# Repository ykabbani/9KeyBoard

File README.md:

# 9-KeyBoard - Custom Mechanical Keyboard

## Project Description

This project was my first attempt at designing and creating a fully functional PCB. The goal of this project was to create a prototype board - hence the 9 keys only, for what will be a full sized keyboard at some point in the future. Once the functionality is verified, the focus will divert to the 60% version of the keyboard (60% refers to 60% of a full sized keyboard, aka keyboard without the numpad or the function key row).

## Schematic

The schematic of the 9-KeyBoard is split into 4 different sections: uC, USB Interface, LED controller, and finally the keyboard's physical keys. Once the functionality of the 9-KeyBoard is verified, the only thing that will need to be changed is the key matrix. The schematic can be seen below: 

## PCB Layout

The component placement on the PCB is necessary after finishing the schematic. The components need to be placed in an optimal manner and the traces need to be routed to connect all the components together. This results in the following PCB and PCB render:

PCB Layout                 |  Top View of Render       |   Bottom View of Render
:-------------------------:|:-------------------------:|:-------------------------:
 |   | 

(Note that the missing components in the renders are due to the use of component libraries that do not contain models to be used in the renders) 

## Fabricated PCB

The final iteration of the prototype 9-KeyBoard was sent out to a fab house and once it arrived all traces were tested for continuity. Then, all components were installed and soldered with a hot air station. This was my first attempt at soldering with a hot air station, so it was not the cleanest job ever.

Bare PCB                   | Assembled & Soldered PCB             
:-------------------------:|:-------------------------:
 | 

## 9-KeyBoard RGB Demo

After verifying that everything was soldered properly, the 9-KeyBoard was plugged into the computer and the OS was flashed using a hex flasher. The ATMEGA32U4 uC comes from the factory with DFU (default bootloader), so flashing it was straight forward. Below is an RGB demo of it.

The 8 key was programmed to function as an RGB cycle button, while the 9 key was programmed to toggle RGB on/off.

RGB Demo                   |
:-------------------------:|
<video src="https://user-images.githubusercontent.com/26261828/186813127-bb65a537-f33c-4e9b-bb25-f617e034cc23.mp4" width="250" /> |

Notice that PCB had to be flipped 180 degrees so that the light can shine through the legends on the keycaps. This is due to a design flaw, as the RGB LEDs need to be placed directly above the switches rather than below them (since the legends are usually located on the upper-most edge of the keycap).

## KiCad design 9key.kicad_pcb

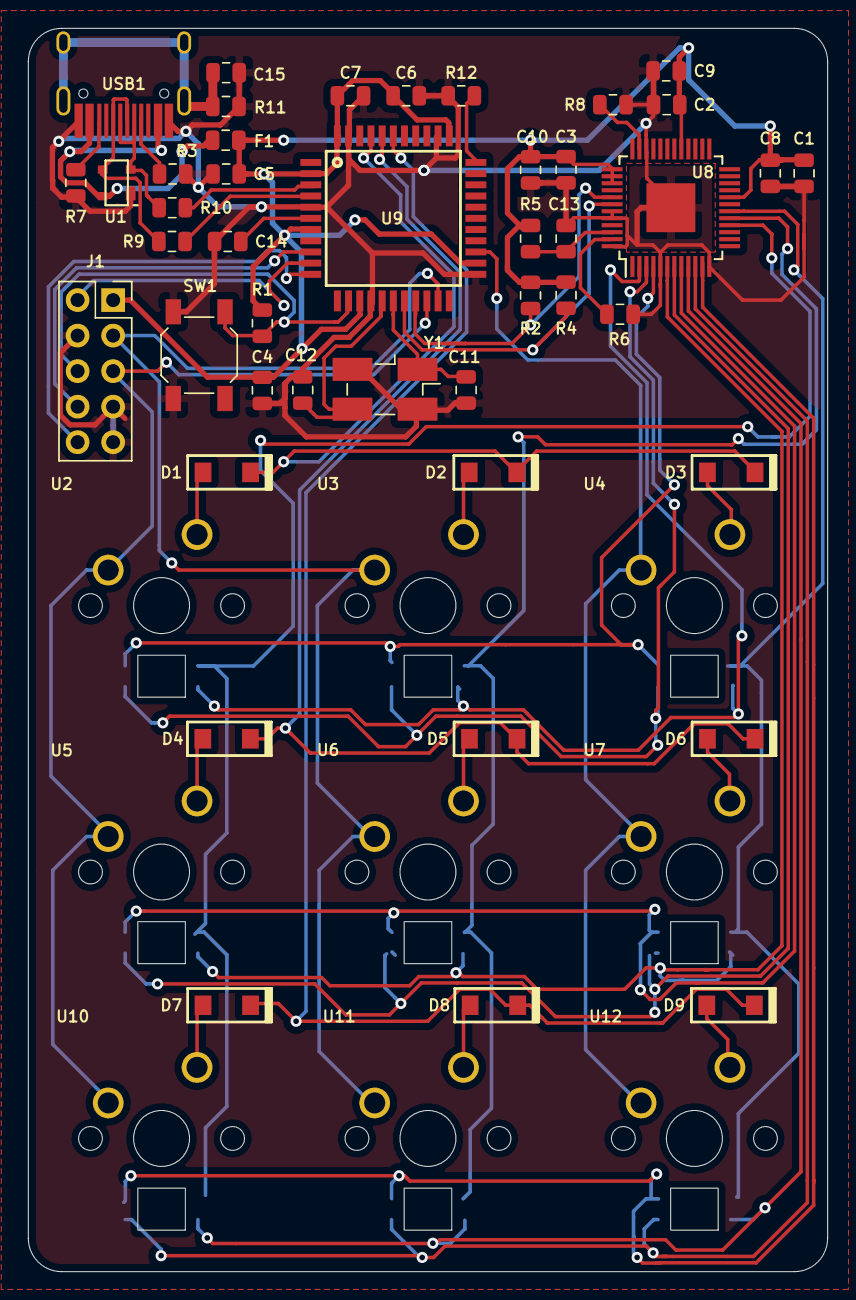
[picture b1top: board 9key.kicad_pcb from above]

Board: 2 copper layers, 57.2 x 88.9 mm, 53 parts (0 on the bottom side), 50 nets.

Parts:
C1, C2, C3: 0.47uF; C_0805_2012Metric
C4, C5, C6, C8, C9, C10: 0.1uF; C_0805_2012Metric
C7: 10uF; C_0805_2012Metric
C11, C12: 22pF; C_0805_2012Metric
C13, C14: 1uF; C_0805_2012Metric
C15: 4.7nF; C_0805_2012Metric
D1, D2, D3, D4, D5, D6, D7, D8, D9: D_Small; D_SOD123
F1: Polyfuse_Small; Fuse_0805_2012Metric
J1: Conn_02x05_Odd_Even; PinSocket_2x05_P2.54mm_Vertical
R1, R5, R12: 10k; R_0805_2012Metric
R2: 1k; R_0805_2012Metric
R3, R7: 5.1k; R_0805_2012Metric
R4: 1K; R_0805_2012Metric
R6: 100k; R_0805_2012Metric
R8: 20k; R_0805_2012Metric
R9, R10: 22; R_0805_2012Metric
R11: 1M; R_0805_2012Metric
SW1: SW_Push; SW_SPST_SKQG_WithStem
U1: PRTR5V0U2X; SOT-143B
U2, U3, U4, U5, U6, U7, U10, U11, U12: Cherry_MX_RGB; Cherry-MX_PCB-Mounted_Rerverse-Mounted-RGB
U8: IS31FL3733-TQ; TQFP-48-1EP_7x7mm_P0.5mm_EP3.5x3.5mm
U9: ATmega32U4-AU; ATMEGA32U4-AU
USB1: HRO-TYPE-C-31-M-12; HRO-TYPE-C-31-M-12-HandSoldering
Y1: 16MHz; Crystal_SMD_EuroQuartz_MJ-4Pin_5.0x3.2mm_HandSoldering

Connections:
+5V: C1.1, C2.1, C3.1, C4.1, C5.1, C6.1, C7.1, C8.1, C9.1, C10.1, F1.1, J1.1, R1.1, R2.2, R4.2, R5.2, U8.20, U8.29, U8.37, U8.38, U8.39, U9.2, U9.7, U9.14, U9.24, U9.34, U9.44
C1: J1.5, U2.5, U5.5, U9.20, U10.5
C2: J1.3, U3.5, U6.5, U9.21, U11.5
C3: U4.5, U7.5, U9.25, U12.5
CS1: U2.4, U5.4, U8.16, U10.4
CS2: U3.4, U6.4, U8.17, U11.4
CS3: U4.4, U7.4, U8.18, U12.4
D+: R9.2, U1.3, USB1.6, USB1.8
D-: R10.2, U1.2, USB1.5, USB1.7
GND: C1.2, C2.2, C3.2, C4.2, C5.2, C6.2, C7.2, C8.2, C9.2, C10.2, C11.2, C12.2, C13.2, C14.1, C15.2, J1.4, J1.7, J1.9, R3.1, R6.2, R7.1, R8.1, R11.2, R12.1, SW1.1, U1.1, U8.5, U8.12, U8.34, U8.43, U8.44, U8.48, U8.49, U9.5, U9.15, U9.23, U9.35, U9.43, USB1.1, USB1.12, Y1.2, Y1.4
MISO: J1.10, U9.11
MOSI: J1.2, U9.10
unnamed: C11.1, U9.17, Y1.1
unnamed: C12.1, U9.16, Y1.3
unnamed: C13.1, R5.1, U8.46
unnamed: C14.2, U9.6
unnamed: C15.1, R11.1, USB1.13
unnamed: D1.2, U2.6
unnamed: D2.2, U3.6
unnamed: D3.2, U4.6
unnamed: D4.2, U5.6
unnamed: D5.2, U6.6
unnamed: D6.2, U7.6
unnamed: D7.2, U10.6
unnamed: D8.2, U11.6
unnamed: D9.2, U12.6
unnamed: R3.2, USB1.4
unnamed: R6.1, U8.47
unnamed: R7.2, USB1.10
unnamed: R8.2, U8.35
unnamed: R9.1, U9.4
unnamed: R10.1, U9.3
unnamed: R12.2, U9.33
R1: D1.1, D2.1, D3.1, U9.41
R2: D4.1, D5.1, D6.1, U9.40
R3: D7.1, D8.1, D9.1, U9.39
RST: J1.6, R1.2, SW1.2, U9.13
SCK: J1.8, U9.9
SCL: R4.1, U8.42, U9.18
SDA: R2.1, U8.41, U9.19
SW1: U2.3, U3.3, U4.3, U8.2
SW2: U2.2, U3.2, U4.2, U8.3
SW3: U2.1, U3.1, U4.1, U8.4
SW4: U5.3, U6.3, U7.3, U8.6
SW5: U5.2, U6.2, U7.2, U8.7
SW6: U5.1, U6.1, U7.1, U8.8
SW7: U8.9, U10.3, U11.3, U12.3
SW8: U8.10, U10.2, U11.2, U12.2
SW9: U8.11, U10.1, U11.1, U12.1
VBUS: F1.2, U1.4, USB1.2, USB1.11

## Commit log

2020-08-07 Created project files
    Made new project
2020-08-07 Add submodules
2020-08-07 Added footprint libraries
2022-08-26 Update README.md
    Uploaded project description + images + demo video
2022-08-26 Housekeeping
    Updated files included in the project and organized libraries into their own folder.
